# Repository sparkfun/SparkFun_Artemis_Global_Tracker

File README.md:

SparkFun Artemis Global Tracker
===============================

[*SparkFun Artemis Global Tracker (WRL-18712)*](https://www.sparkfun.com/products/18712)

The SparkFun Artemis Global Tracker combines the SparkFun Artemis processor with an Iridium 9603N satellite transceiver, ZOE-M8Q GNSS transceiver, and MS8607 PHT sensor to create a truly global tracking and data gathering device in a small form-factor. With a clear view of the sky, this board allows you to send and receive short data messages from anywhere in the world including remote locations like the polar regions, far beyond the reach of WiFi and GSM networks.

Repository Contents
-------------------

* **/Documentation** - Datasheets, FAQs, Hardware Overview, and Message Format for the full Global Tracker Example
* **/Hardware** - Eagle PCB, SCH and LBR design files
* **/Software** - Arduino examples
* **/Tools** - Tools to help: configure the full GlobalTracker example via USB or remotely via Iridium messaging; and track and map its position
* **/binaries** - binary files for the examples which you can upload using the [Artemis Firmware Upload GUI](https://github.com/sparkfun/Artemis-Firmware-Upload-GUI) instead of the Arduino IDE
* **/img** - Folder hosting for images used in the repository
* **LICENSE.md** contains the licence information

Documentation
-------------

* **[Hookup Guide](https://learn.sparkfun.com/tutorials/artemis-global-tracker-hookup-guide)** - Hookup Guide for the SparkFun Artemis Global Tracker.
* **[Artemis Development with Arduino](https://learn.sparkfun.com/tutorials/artemis-development-with-the-arduino-ide)** - An in-depth guide on developing in the Arduino IDE for the Artemis module and any Artemis microcontroller development board.
* **[SparkFun Apollo3 Arduino Core](https://github.com/sparkfun/Arduino_Apollo3)** - GitHub Repository for the SparkFun Apollo3 Arduino core.
* **[Installing an Arduino Library Guide](https://learn.sparkfun.com/tutorials/installing-an-arduino-library)** - Basic information on how to install an Arduino library.
* **[SparkFun IridiumSBD I<sup>2</sup>C Arduino Library](https://github.com/sparkfun/SparkFun_IridiumSBD_I2C_Arduino_Library)** - An Arduino library to support Short Burst Data communication using the Iridium 9602 and 9603N over both Serial and I2C.
* **[SparkFun u-blox GNSS Arduino Library](https://github.com/sparkfun/SparkFun_u-blox_GNSS_Arduino_Library)** - An Arduino library which allows you to communicate seamlessly with the full range of u-blox GNSS modules.
* **[SparkFun MS8607 Arduino Library](https://github.com/sparkfun/SparkFun_PHT_MS8607_Arduino_Library)** - An Arduino library for the TE MS8607 combined Pressure, Humidity and Temperature sensor.

Version History
---------------

* [SPX-16469](https://www.sparkfun.com/products/16469) - Initial SparkX Release
* [WRL-18712](https://www.sparkfun.com/products/18712) - Initial SparkFun Release

License Information
-------------------

This product is _**open source**_!

Please review the LICENSE.md file for license information.

If you have any questions or concerns on licensing, please contact technical support on our [SparkFun forums](https://forum.sparkfun.com/viewforum.php?f=123).

Distributed as-is; no warranty is given.

- Your friends at SparkFun.

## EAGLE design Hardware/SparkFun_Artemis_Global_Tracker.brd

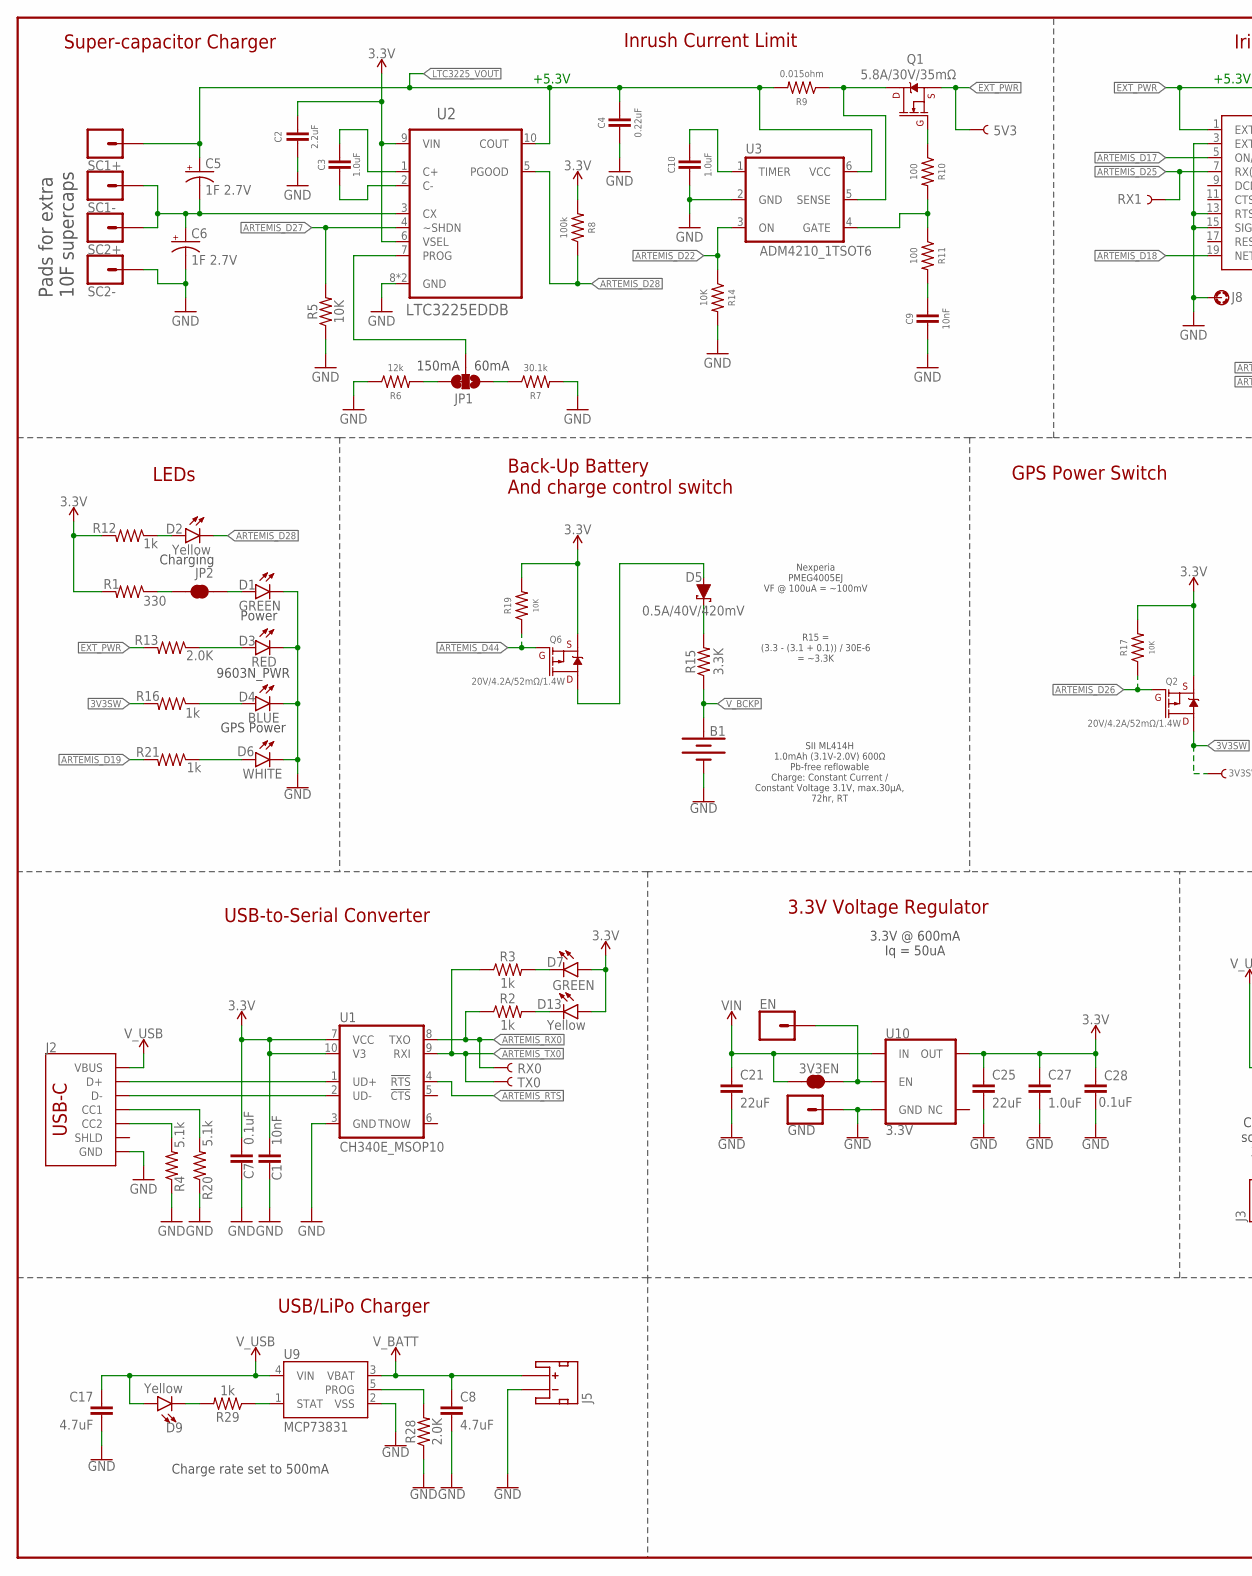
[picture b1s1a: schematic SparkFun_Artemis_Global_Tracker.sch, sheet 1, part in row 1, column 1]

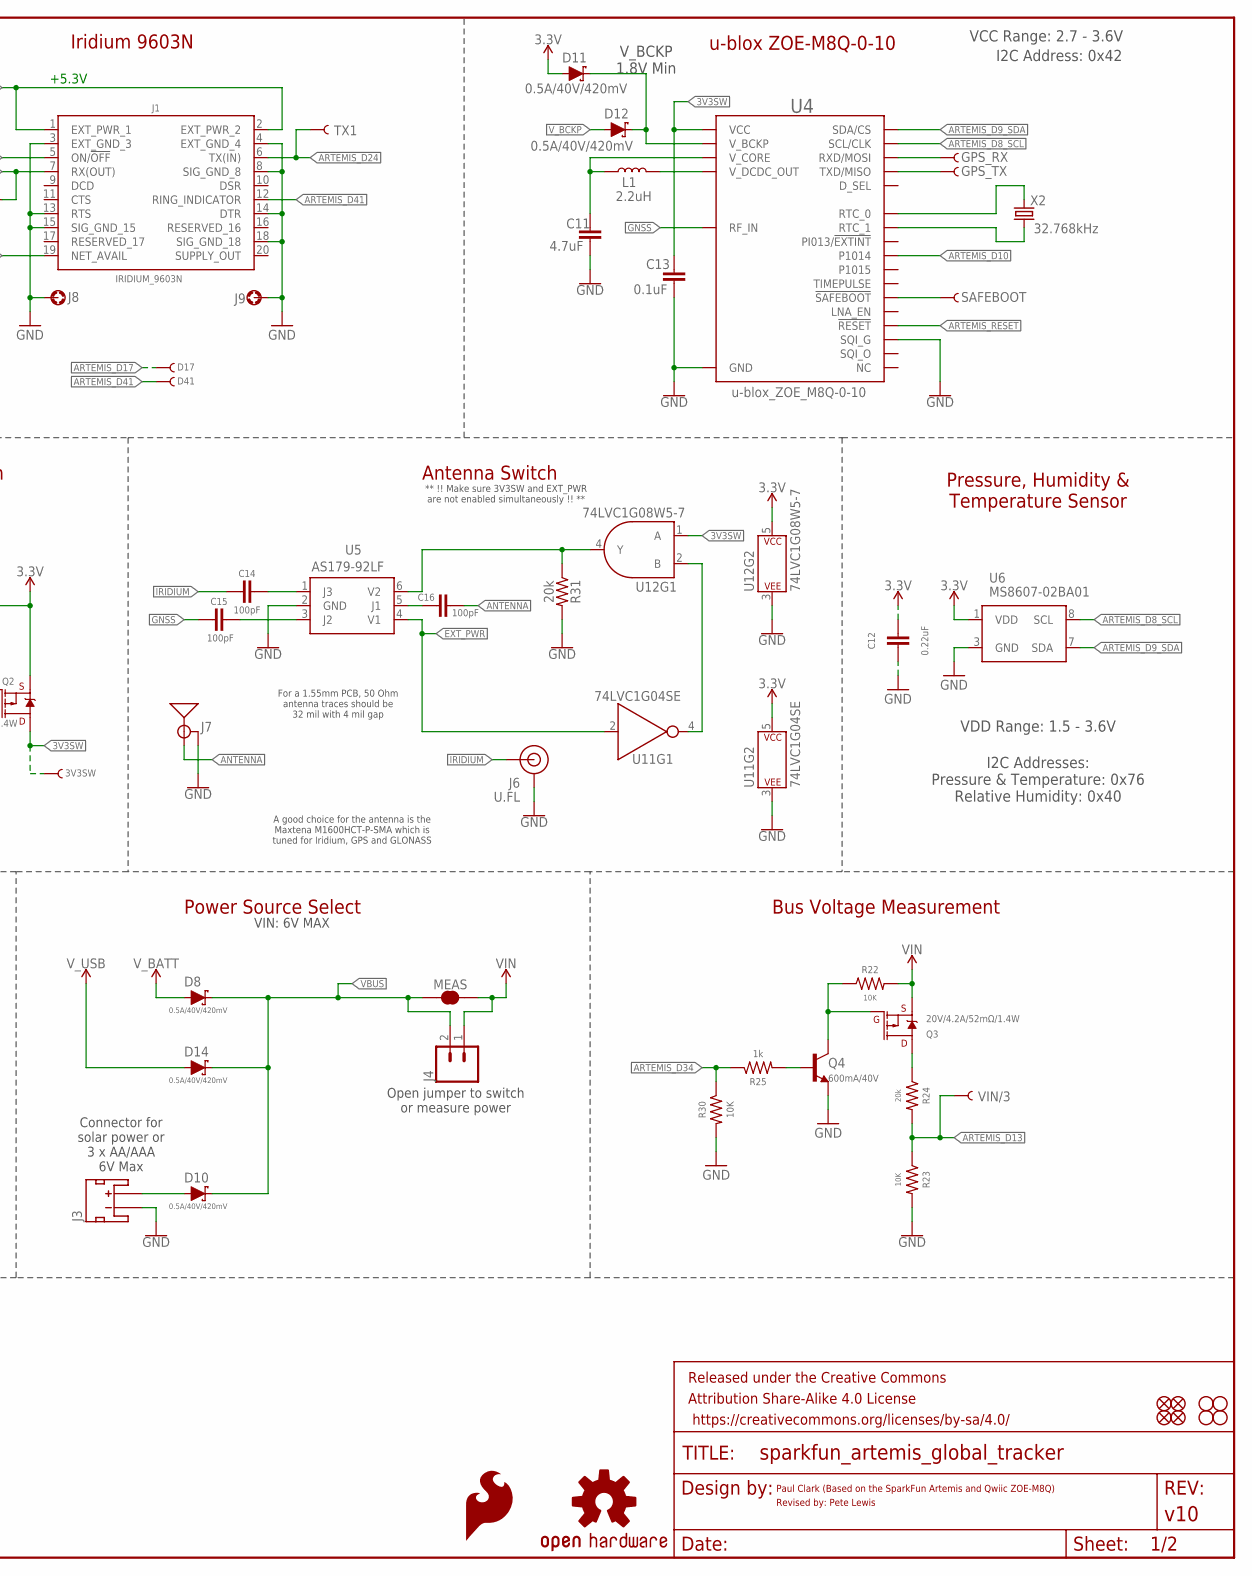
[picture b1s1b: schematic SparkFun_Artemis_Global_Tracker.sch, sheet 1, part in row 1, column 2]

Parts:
3V3EN: JUMPER-SMT_2_NC_TRACE_SILK; SMT-JUMPER_2_NC_TRACE_SILK
3V3SW, 5V3: TEST-POINT3X5; PAD.03X.05
B1: ML414H_IV01E_BATTERY; ML414H_IV01E
C1, C9: 10nF; 0603
C2: 2.2uF; 0603
C3, C10, C27: 1.0uF; 0603
C4, C12: 0.22uF; 0603
C5, C6: 1F 2.7V; CPOL-RADIAL-1F-2.7V
C7, C13, C28: 0.1uF; 0603
C8, C11, C17: 4.7uF; 0603
C14, C15, C16: 100pF; 0603
C21, C25: 22uF; 0805
D1, D7: GREEN; LED-0603
D2, D9, D13: Yellow; LED-0603
D3: RED; LED-0603
D4: BLUE; LED-0603
D5, D8, D10, D11, D12, D14: 0.5A/40V/420mV; SOD-323
D6: WHITE; LED-0603
D17, D41: TEST-POINT3X5; PAD.03X.05
EN: CONN_01PTH_NO_SILK_YES_STOP; 1X01_NO_SILK
FRAME5: FRAME-LEDGER; CREATIVE_COMMONS
GND: CONN_01PTH_NO_SILK_YES_STOP; 1X01_NO_SILK
GPS_RX: TEST-POINT3X5; PAD.03X.05
GPS_TX: TEST-POINT3X5; PAD.03X.05
J1: IRIDIUM_9603N
J2: USB-C; USB-C-16P-2LAYER-PADS
J3, J5: JST_2MM_MALE; JST-2-SMD
J4: CONN_021X02_NO_SILK; 1X02_NO_SILK
J6: U.FL
J7: ANTENNA-GROUNDEDEDGE_SMA; SMA-EDGE
J8, J9: STAND-OFF-REFLOW-M2.0_6.0MM_TALL; STAND-OFF-REFLOW-M2.0
JP1: JUMPER-SMT_3_1-NC_TRACE_SILK; SMT-JUMPER_3_1-NC_TRACE_SILK
JP2: JUMPER-SMT_2_NC_TRACE_SILK; SMT-JUMPER_2_NC_TRACE_SILK
JP7, JP8, JP13, JP14: FIDUCIAL1X2; FIDUCIAL-1X2
JP9, JP10, JP11, JP12: STAND-OFF
L1: 2.2uH; 0806
LOGO2: SFE_LOGO_FLAME.3_INCH; SFE_LOGO_FLAME_.3
LOGO4: OSHW-LOGOMINI; OSHW-LOGO-MINI
MEAS: JUMPER-SMT_2_NC_TRACE_SILK; SMT-JUMPER_2_NC_TRACE_SILK
Q1: 5.8A/30V/35mΩ; SOT23-3
Q2, Q3, Q6: 20V/4.2A/52mΩ/1.4W; SOT23-3
Q4: 600mA/40V; SOT23-3
R1: 330; 0402-TIGHT
R2, R3, R12, R16, R21, R25, R29: 1k; 0402-TIGHT
R4, R20: 5.1k; 0402-TIGHT
R5, R14, R17, R19, R22, R23, R30: 10K; 0402-TIGHT
R6: 12k; 0603
R7: 30.1k; 0603
R8: 100k; 0603
R9: 0.015ohm; 0603
R10, R11: 100; 0402-TIGHT
R13, R28: 2.0K; 0402-TIGHT
R15: 3.3K; 0402-TIGHT
R24: 20k; 0603
R31: 20k; 0402-TIGHT
RX0, RX1: TEST-POINT3X5; PAD.03X.05
SAFEBOOT: TEST-POINT3X5; PAD.03X.05
SC1+, SC1-, SC2+, SC2-: CONN_01PTH_NO_SILK_YES_STOP; 1X01_NO_SILK
TX0, TX1: TEST-POINT3X5; PAD.03X.05
U1: CH340E_MSOP10; MSOP10
U2: LTC3225EDDB; DFN300X200-10L
U3: ADM4210_1TSOT6; TSOT6
U4: u-blox_ZOE_M8Q-0-10; UBLOX_ZOE_M8-0-10
U5: AS179-92LF; SOT65P220X100-6N
U6: MS8607-02BA01
U9: MCP73831; SOT23-5
U10: 3.3V; SOT23-5
U11: 74LVC1G04SE; SOT353
U12: 74LVC1G08W5-7; SOT23-5
VIN/3: TEST-POINT3X5; PAD.03X.05
X2: 32.768kHz; CRYSTAL-SMD-3.2X1.5MM

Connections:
3.3V: C1.1, C2.1, C7.1, C12.1, C25.1, C27.1, C28.1, D7.A, D11.A, D13.A, Q2.2 (S), Q6.2 (S), R1.2, R8.2, R12.2, R17.2, R19.2, U1.7 (VCC), U1.10 (V3), U2.6 (VSEL), U2.9 (VIN), U6.1 (VDD), U10.5 (OUT), U11.5 (P$V+), U12.5 (P$V+); also elsewhere on the board
3V3SW: 3V3SW.1, C13.1, Q2.3 (D), R16.2, U4.24 (VCC), U4.25 (VCC), U12.1 (A)
ANTENNA: C16.1, J7.SIG (SIGNAL)
ARTEMIS_!RESET: U4.20 (!RESET); also elsewhere on the board
ARTEMIS_!RTS!: U1.4 (!RTS); also elsewhere on the board
ARTEMIS_D8_SCL: U4.32 (SCL/CLK), U6.8 (SCL); also elsewhere on the board
ARTEMIS_D9_SDA: U4.2 (SDA/CS), U6.7 (SDA); also elsewhere on the board
ARTEMIS_D10: U4.50 (P1014); also elsewhere on the board
ARTEMIS_D13: R23.1, R24.2, VIN/3.1; also elsewhere on the board
ARTEMIS_D17: D17.1, J1.5 (ON/!OFF!); also elsewhere on the board
ARTEMIS_D18: J1.19 (NET_AVAIL); also elsewhere on the board
ARTEMIS_D19: R21.2; also elsewhere on the board
ARTEMIS_D22: R14.1, U3.3 (ON); also elsewhere on the board
ARTEMIS_D24: J1.6 (TX(IN)), TX1.1; also elsewhere on the board
ARTEMIS_D25: J1.7 (RX(OUT)), RX1.1; also elsewhere on the board
ARTEMIS_D26: Q2.1 (G), R17.1; also elsewhere on the board
ARTEMIS_D27: R5.2, U2.4 (~SHDN); also elsewhere on the board
ARTEMIS_D28: D2.C, R8.1, U2.5 (PGOOD); also elsewhere on the board
ARTEMIS_D34: R25.1, R30.1; also elsewhere on the board
ARTEMIS_D41: D41.1, J1.12 (RING_INDICATOR); also elsewhere on the board
ARTEMIS_D44: Q6.1 (G), R19.1; also elsewhere on the board
ARTEMIS_RX0: R2.1, RX0.1, U1.8 (TXO); also elsewhere on the board
ARTEMIS_TX0: R3.1, TX0.1, U1.9 (RXI); also elsewhere on the board
CC3: J2.B5 (CC2), R4.2
CC4: J2.A5 (CC1), R20.2
D+2: J2.A6 (D+), J2.B6 (D+), U1.1 (UD+)
D-2: J2.A7 (D-), J2.B7 (D-), U1.2 (UD-)
EXT_PWR: 5V3.1, J1.1 (EXT_PWR_1), J1.2 (EXT_PWR_2), Q1.2 (S), R13.2, U5.4 (V1), U11.2 (A)
GND: B1.-, C1.2, C2.2, C4.2, C6.-, C7.2, C8.2, C9.2, C10.2, C11.2, C12.2, C13.2, C17.2, C21.2, C25.2, C27.2, C28.2, D1.C, D3.C, D4.C, D6.C, GND.1, J1.3 (EXT_GND_3), J1.4 (EXT_GND_4), J1.8 (SIG_GND_8), J1.13 (RTS), J1.14 (DTR), J1.15 (SIG_GND_15), J1.18 (SIG_GND_18), J2.GND, J2.GND2 (GND), J3.1 (-), J5.1 (-), J6.1 (GND), J6.2 (GND), J7.GND@0 (GND), J7.GND@1 (GND), J7.GND@2 (GND), J7.GND@3 (GND), J8.1, J9.1, Q4.2 (E), R4.1, R5.1, R6.1, R7.2, R14.2, R20.1, R23.2, R28.1, R30.2, R31.2, SC2-.1, U1.3 (GND), U2.8 (GND), U2.11 (GND), U3.2 (GND), U4.1 (GND), U4.3 (GND), U4.5 (GND), U4.7 (GND), U4.8 (GND), U4.9 (GND), U4.10 (GND), U4.11 (GND), U4.12 (GND), U4.17 (GND), U4.23 (GND), U4.29 (SQI_G), U4.31 (SQI_G), U4.37 (GND), U4.38 (GND), U4.39 (GND), U4.40 (GND), U4.41 (GND), U4.44 (GND), U4.46 (SQI_G), U4.47 (SQI_G), U4.49 (GND), U5.2 (GND), U6.3 (GND), U9.2 (VSS), U10.2 (GND), U11.3 (P$V-), U12.3 (P$V-); also elsewhere on the board
GNSS: C15.2, U4.4 (RF_IN)
IRIDIUM: C14.2, J6.FEED (SIGNAL)
LTC3225_VOUT: C4.1, C5.+, R9.2, SC1+.1, U2.10 (COUT), U3.6 (VCC)
unnamed: C5.-, C6.+, SC1-.1, SC2+.1, U2.3 (CX)
unnamed: JP1.3, R6.2
unnamed: JP2.2, R1.1
unnamed: JP1.1, R7.1
unnamed: D2.A, R12.1
unnamed: D3.A, R13.1
unnamed: D5.A, Q6.3 (D)
unnamed: Q1.3 (D), R9.1, U3.5 (SENSE)
unnamed: C3.2, U2.2 (C-)
unnamed: C3.1, U2.1 (C+)
unnamed: JP1.2, U2.7 (PROG)
unnamed: Q1.1 (G), R10.1
unnamed: R10.2, R11.1, U3.4 (GATE)
unnamed: C9.1, R11.2
unnamed: C10.1, U3.1 (TIMER)
unnamed: L1.2, U4.26 (V_DCDC_OUT)
unnamed: C11.1, L1.1, U4.27 (V_CORE)
unnamed: U4.18 (RTC_0), X2.P$2 (2)
unnamed: U4.19 (RTC_1), X2.P$1 (1)
unnamed: D5.C, R15.2
unnamed: D4.A, R16.1
unnamed: D13.C, R2.2
unnamed: D1.A, JP2.1
unnamed: D11.C, D12.C, U4.16 (V_BCKP)
unnamed: SAFEBOOT.1, U4.34 (!SAFEBOOT)
unnamed: GPS_RX.1, U4.22 (RXD/MOSI)
unnamed: GPS_TX.1, U4.21 (TXD/MISO)
unnamed: C14.1, U5.1 (J3)
unnamed: C15.1, U5.3 (J2)
unnamed: C16.2, U5.5 (J1)
unnamed: R31.1, U5.6 (V2), U12.4 (Y)
unnamed: D7.C, R3.2
unnamed: U11.4 (Y), U12.2 (B)
unnamed: D6.A, R21.1
unnamed: 3V3EN.2, EN.1, U10.3 (EN)
unnamed: Q3.1 (G), Q4.3 (C), R22.1
unnamed: R28.2, U9.5 (PROG)
unnamed: D9.C, R29.2
unnamed: R29.1, U9.1 (STAT)
unnamed: Q3.3 (D), R24.1
unnamed: Q4.1 (B), R25.2
VBUS: D8.C, D10.C, D14.C, J4.2, MEAS.1
VIN: 3V3EN.1, C21.1, J4.1, MEAS.2, Q3.2 (S), R22.2, U10.1 (IN)
V_AAA: D10.A, J3.2 (+)
V_BATT: C8.1, D8.A, J5.2 (+), U9.3 (VBAT)
V_BCKP: B1.+, D12.A, R15.1
V_USB: C17.1, D9.A, D14.A, J2.VBUS1 (VBUS), J2.VBUS2 (VBUS), U9.4 (VIN)

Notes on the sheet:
Paul Clark (Based on the SparkFun Artemis and Qwiic ZOE-M8Q)
Power
+5.3V
150mA
60mA
Pads for extra 10F supercaps
Super-capacitor Charger
Charging
9603N_PWR
Iridium 9603N
LEDs
Inrush Current Limit
GPS Power
u-blox ZOE-M8Q-0-10
VCC Range: 2.7 - 3.6V
I2C Address: 0x42
V_BCKP 1.8V Min
Back-Up Battery And charge control switch
SII ML414H 1.0mAh (3.1V-2.0V) 600Ω Pb-free reflowable Charge: Constant Current / Constant Voltage 3.1V, max.30μA, 72hr, RT
Nexperia PMEG4005EJ VF @ 100uA = ~100mV
R15 = (3.3 - (3.1 + 0.1)) / 30E-6 = ~3.3K
GPS Power Switch
Antenna Switch
** !! Make sure 3V3SW and EXT_PWR are not enabled simultaneously !! **
A good choice for the antenna is the Maxtena M1600HCT-P-SMA which is tuned for Iridium, GPS and GLONASS
For a 1.55mm PCB, 50 Ohm antenna traces should be 32 mil with 4 mil gap
Pressure, Humidity & Temperature Sensor
VDD Range: 1.5 - 3.6V
I2C Addresses: Pressure & Temperature: 0x76 Relative Humidity: 0x40
USB-to-Serial Converter
3.3V @ 600mA Iq = 50uA
USB/LiPo Charger
Charge rate set to 500mA
Power Source Select
Open jumper to switch or measure power
Connector for solar power or 3 x AA/AAA 6V Max
Bus Voltage Measurement
Revised by: Pete Lewis
VIN: 6V MAX
3.3V Voltage Regulator

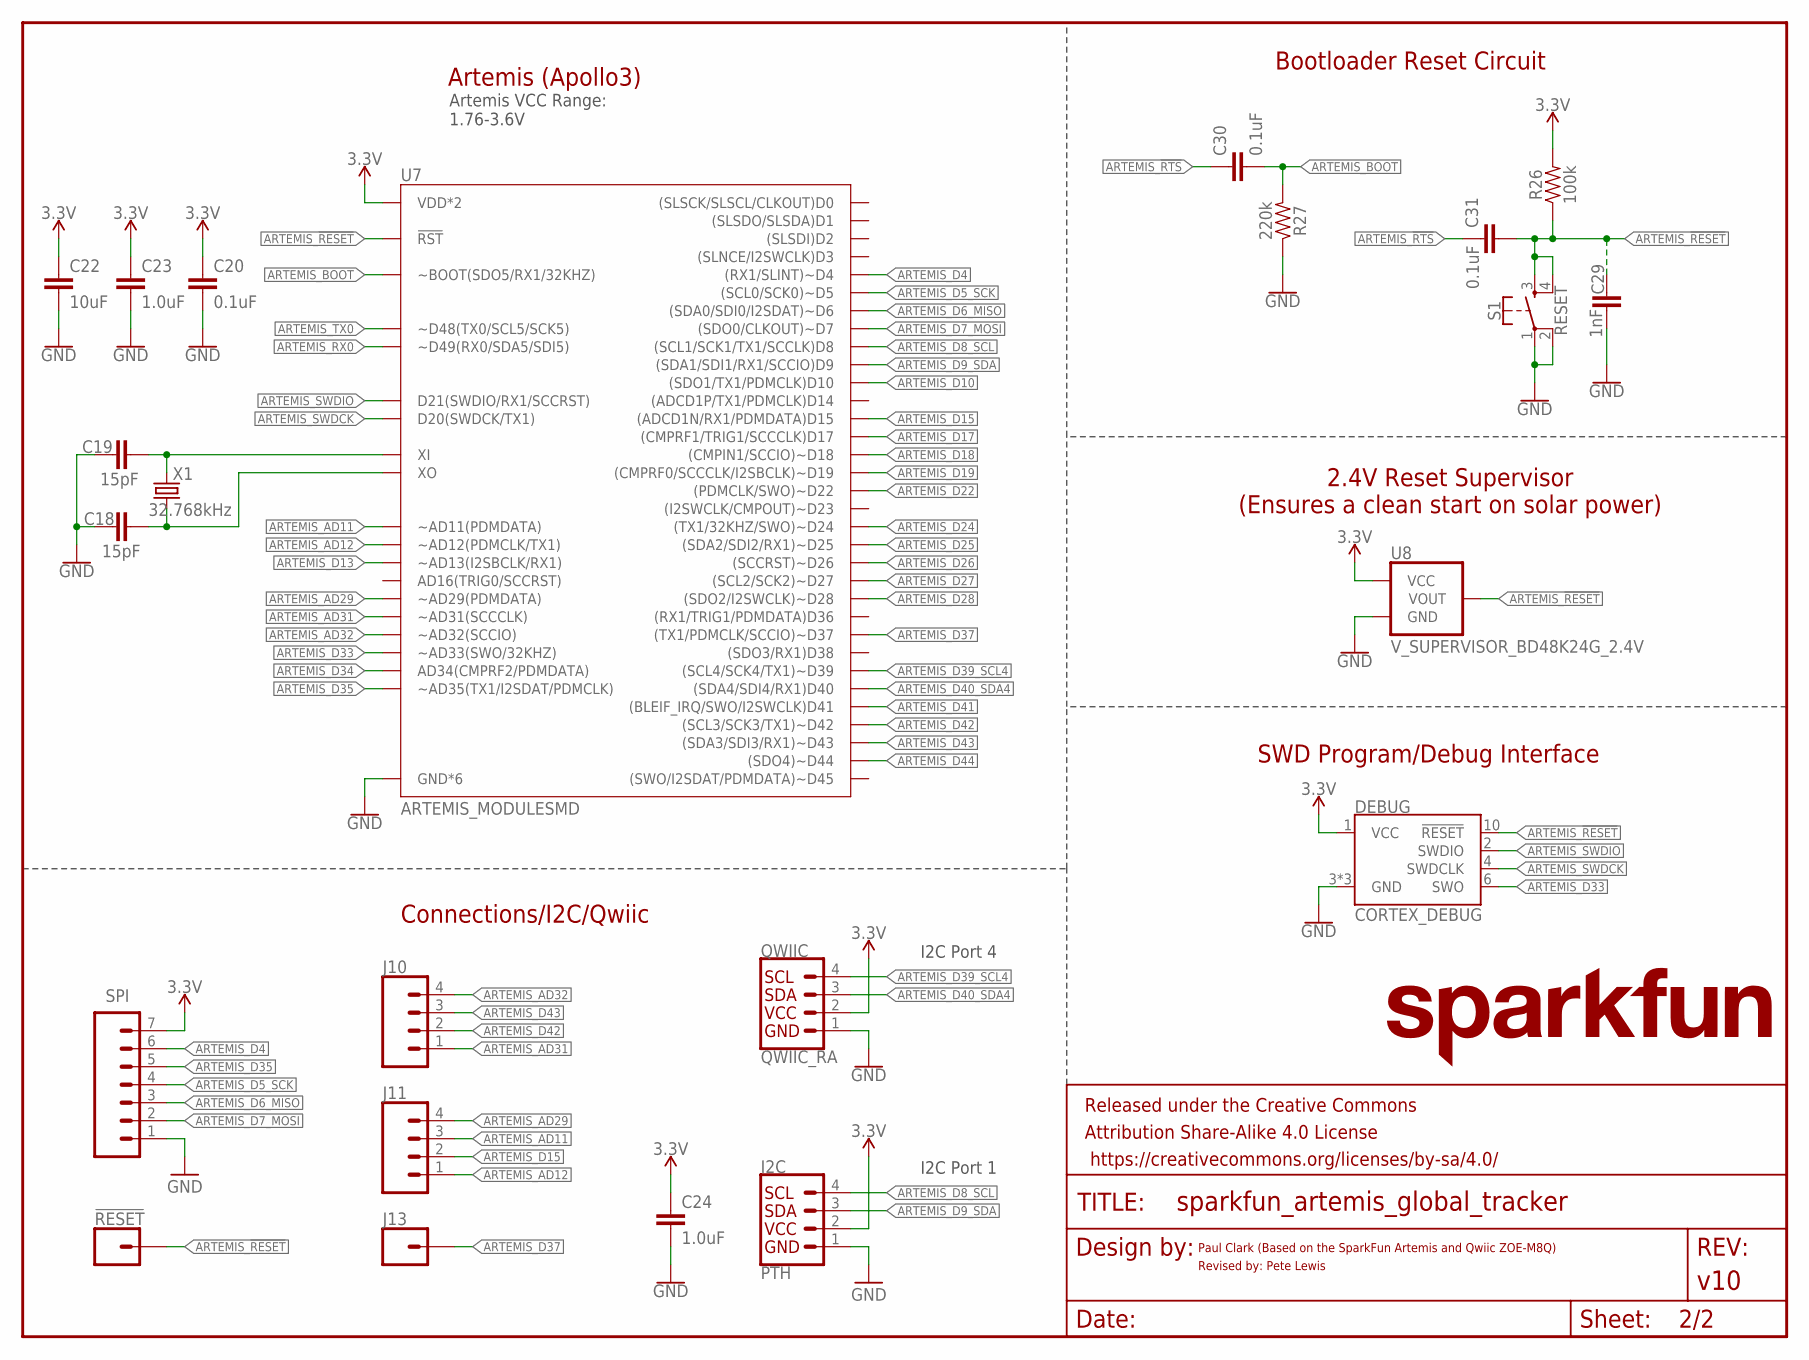
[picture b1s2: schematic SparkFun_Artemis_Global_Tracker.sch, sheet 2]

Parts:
!RESET: CONN_01PTH_NO_SILK_YES_STOP; 1X01_NO_SILK
C18, C19: 15pF; 0603
C20, C30, C31: 0.1uF; 0603
C22: 10uF; 0603
C23, C24: 1.0uF; 0603
C29: 1nF; 0603
DEBUG: CORTEX_DEBUG; 2X5-PTH-1.27MM-NO_SILK
FRAME3: FRAME-LETTERNO_PACKAGE; DUMMY
I2C: PTH; 1X04_NO_SILK
J10, J11: CONN_041X04_NO_SILK_NO_POP; 1X04_NO_SILK
J13: CONN_01PTH_NO_SILK_YES_STOP; 1X01_NO_SILK
LOGO1: SFE_LOGO_NAME.1_INCH; SFE_LOGO_NAME_.1
QWIIC: QWIIC_RA; JST04_1MM_RA
R26: 100k; 0603
R27: 220k; 0603
S1: RESET; TACTILE_SWITCH_SMD_5.2MM
SPI: CONN_07NO_SILK; 1X07_NO_SILK
U7: ARTEMIS_MODULESMD; ARTEMIS_FP
U8: V_SUPERVISOR_BD48K24G_2.4V; SOT23-3
X1: 32.768kHz; CRYSTAL-SMD-3.2X1.5MM

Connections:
3.3V: C20.2, C22.1, C23.1, C24.1, DEBUG.1 (VCC), I2C.2, QWIIC.2, R26.2, SPI.7, U7.VDD@36 (VDD*2), U7.VDD@37 (VDD*2), U8.3 (VCC); also elsewhere on the board
ARTEMIS_!RESET: !RESET.1, C29.1, C31.2, DEBUG.10 (!RESET), R26.1, S1.3, S1.4, U7.~RST (!RST), U8.2 (VOUT); also elsewhere on the board
ARTEMIS_!RTS!: C30.1, C31.1; also elsewhere on the board
ARTEMIS_AD11: J11.3, U7.~AD11 (~AD11(PDMDATA))
ARTEMIS_AD12: J11.1, U7.~AD12 (~AD12(PDMCLK/TX1))
ARTEMIS_AD29: J11.4, U7.~AD29 (~AD29(PDMDATA))
ARTEMIS_AD31: J10.1, U7.~AD31 (~AD31(SCCCLK))
ARTEMIS_AD32: J10.4, U7.~AD32 (~AD32(SCCIO))
ARTEMIS_BOOT: C30.2, R27.2, U7.BOOT (~BOOT(SDO5/RX1/32KHZ))
ARTEMIS_D4: SPI.6, U7.~D4 ((RX1/SLINT)~D4)
ARTEMIS_D5_SCK: SPI.4, U7.~D5 ((SCL0/SCK0)~D5)
ARTEMIS_D6_MISO: SPI.3, U7.~D6 ((SDA0/SDI0/I2SDAT)~D6)
ARTEMIS_D7_MOSI: SPI.2, U7.D7 ((SDO0/CLKOUT)~D7)
ARTEMIS_D8_SCL: I2C.4, U7.D8 ((SCL1/SCK1/TX1/SCCLK)D8); also elsewhere on the board
ARTEMIS_D9_SDA: I2C.3, U7.D9 ((SDA1/SDI1/RX1/SCCIO)D9); also elsewhere on the board
ARTEMIS_D10: U7.D10 ((SDO1/TX1/PDMCLK)D10); also elsewhere on the board
ARTEMIS_D13: U7.~AD13 (~AD13(I2SBCLK/RX1)); also elsewhere on the board
ARTEMIS_D15: J11.2, U7.D15 ((ADCD1N/RX1/PDMDATA)D15)
ARTEMIS_D17: U7.D17 ((CMPRF1/TRIG1/SCCCLK)D17); also elsewhere on the board
ARTEMIS_D18: U7.~D18 ((CMPIN1/SCCIO)~D18); also elsewhere on the board
ARTEMIS_D19: U7.~D19 ((CMPRF0/SCCCLK/I2SBCLK)~D19); also elsewhere on the board
ARTEMIS_D22: U7.~D22 ((PDMCLK/SWO)~D22); also elsewhere on the board
ARTEMIS_D24: U7.~D24 ((TX1/32KHZ/SWO)~D24); also elsewhere on the board
ARTEMIS_D25: U7.~D25 ((SDA2/SDI2/RX1)~D25); also elsewhere on the board
ARTEMIS_D26: U7.~D26 ((SCCRST)~D26); also elsewhere on the board
ARTEMIS_D27: U7.~D27 ((SCL2/SCK2)~D27); also elsewhere on the board
ARTEMIS_D28: U7.~D28 ((SDO2/I2SWCLK)~D28); also elsewhere on the board
ARTEMIS_D33: DEBUG.6 (SWO), U7.~AD33/SWO (~AD33(SWO/32KHZ))
ARTEMIS_D34: U7.AD34 (AD34(CMPRF2/PDMDATA)); also elsewhere on the board
ARTEMIS_D35: SPI.5, U7.~AD35 (~AD35(TX1/I2SDAT/PDMCLK))
ARTEMIS_D37: J13.1, U7.~D37 ((TX1/PDMCLK/SCCIO)~D37)
ARTEMIS_D39_SCL4: QWIIC.4, U7.~D39 ((SCL4/SCK4/TX1)~D39)
ARTEMIS_D40_SDA4: QWIIC.3, U7.D40 ((SDA4/SDI4/RX1)D40)
ARTEMIS_D41: U7.D41 ((BLEIF_IRQ/SWO/I2SWCLK)D41); also elsewhere on the board
ARTEMIS_D42: J10.2, U7.~D42 ((SCL3/SCK3/TX1)~D42)
ARTEMIS_D43: J10.3, U7.~D43 ((SDA3/SDI3/RX1)~D43)
ARTEMIS_D44: U7.~D44 ((SDO4)~D44); also elsewhere on the board
ARTEMIS_RX0: U7.RXI-0 (~D49(RX0/SDA5/SDI5)); also elsewhere on the board
ARTEMIS_SWDCK: DEBUG.4 (SWDCLK), U7.SWDCK (D20(SWDCK/TX1))
ARTEMIS_SWDIO: DEBUG.2 (SWDIO), U7.SWDIO (D21(SWDIO/RX1/SCCRST))
ARTEMIS_TX0: U7.TXO-0 (~D48(TX0/SCL5/SCK5)); also elsewhere on the board
GND: C18.1, C19.1, C20.1, C22.2, C23.2, C24.2, C29.2, DEBUG.3 (GND), DEBUG.5 (GND), DEBUG.9 (GND), I2C.1, QWIIC.1, R27.1, S1.1, S1.2, SPI.1, U7.GND@1 (GND*6), U7.GND@22 (GND*6), U7.GND@38 (GND*6), U7.GND@39 (GND*6), U7.GND@47 (GND*6), U7.GND@59 (GND*6), U8.1 (GND); also elsewhere on the board
XTALI: C19.2, U7.XI, X1.P$1 (1)
XTALO: C18.2, U7.XO, X1.P$2 (2)

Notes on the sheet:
Artemis (Apollo3)
Artemis VCC Range: 1.76-3.6V
Bootloader Reset Circuit
SWD Program/Debug Interface
Connections/I2C/Qwiic
I2C Port 1
I2C Port 4
2.4V Reset Supervisor (Ensures a clean start on solar power)
Paul Clark (Based on the SparkFun Artemis and Qwiic ZOE-M8Q)
Revised by: Pete Lewis

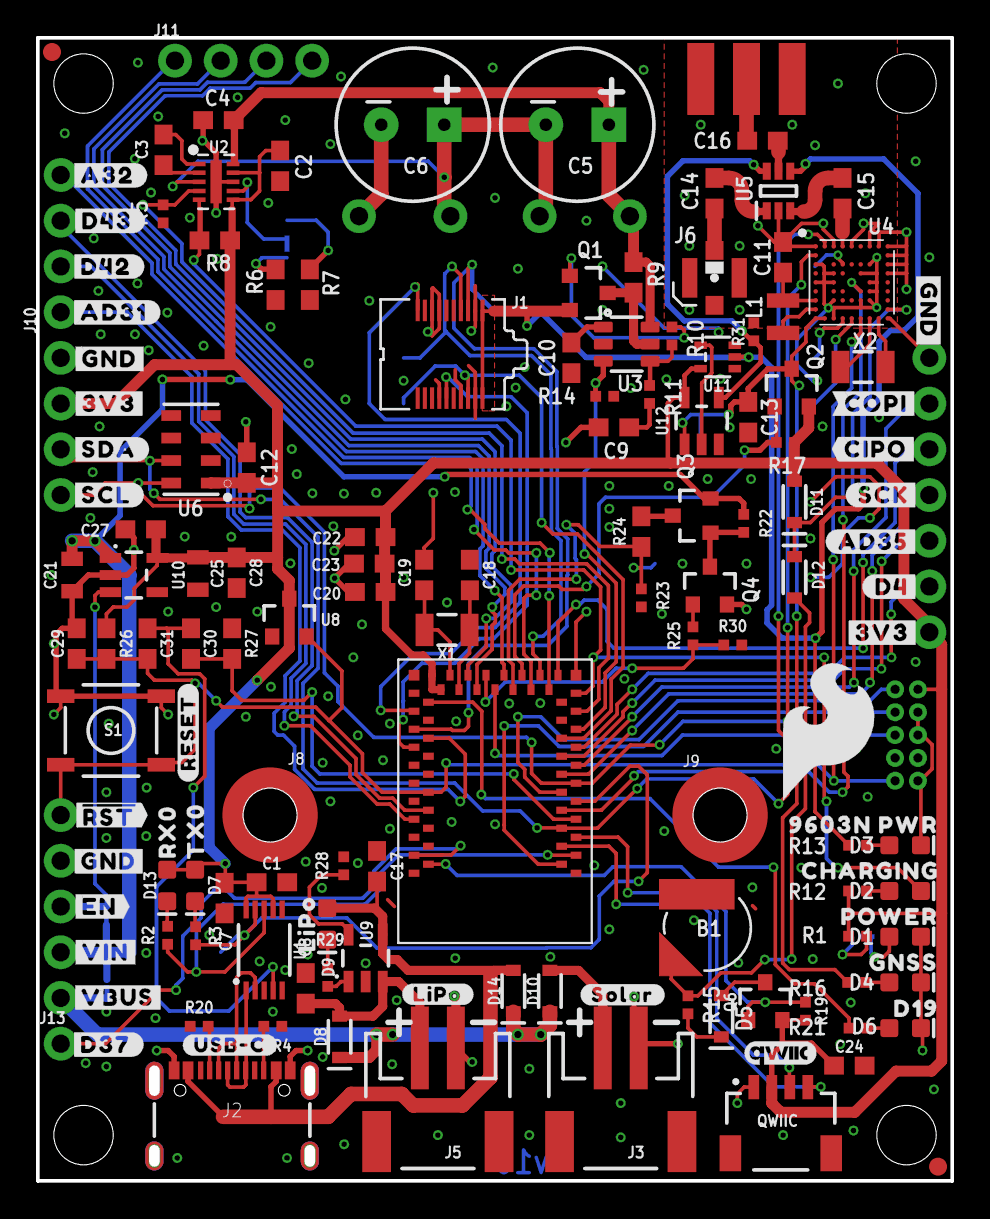
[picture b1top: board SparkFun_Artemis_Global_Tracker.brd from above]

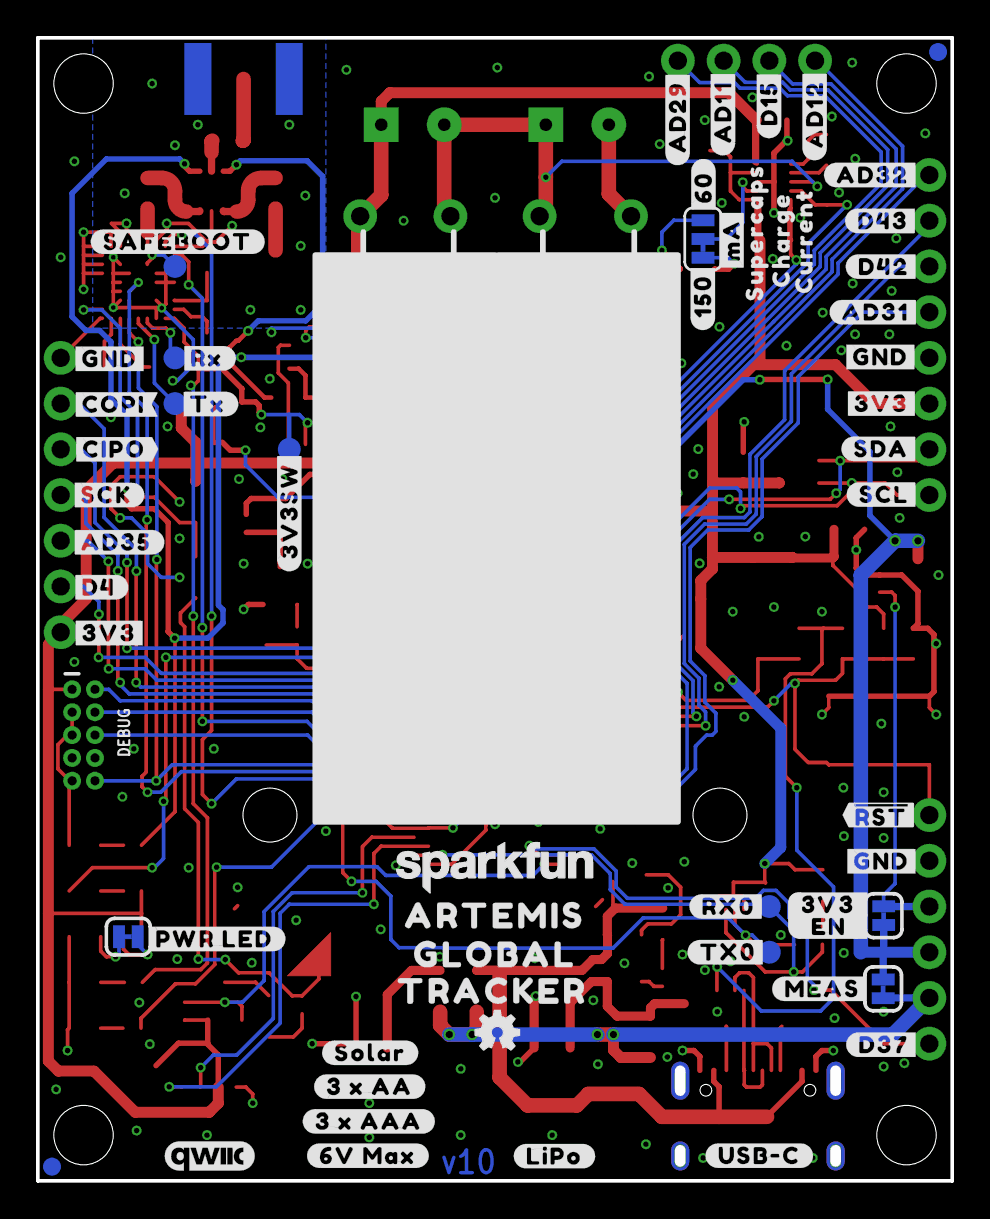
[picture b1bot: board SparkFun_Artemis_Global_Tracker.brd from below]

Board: 2 copper layers, 50.8 x 63.5 mm, 240 parts (79 on the bottom side), 101 nets.

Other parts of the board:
U$1, U$13: SUPERCAPACITOR151
U$2: #SCK#199608
U$3, U$43: #3V3#0
U$4: #SDA#0
U$5: #USB#C#0
U$6: #SCL#0
U$7: #VIN#158
U$8: #3V3SW#0
U$9: CHARGING9604
U$10: #COPI#9694
U$11: QWIIC_4MM
U$12: LIPO5
U$14, U$15: 10F_2#7V152
U$16: RX06
U$17, U$70: #3V3#153
U$18: TX07
U$19: #AD35#199609
U$20, U$36: #GND#0
U$21: #SDA#153
U$22: #SCL#154
U$24: #AD31#7
U$25: QWIIC_5MM
U$26: #_RST##156
U$27: #EN#157
U$28: #VIN#3#0
U$29: #AD35#0
U$30: ARTEMIS0
U$31: SUPERCAPS6
U$32: #D17#0
U$33: #SAFEBOOT#0
U$34: #TX0#0
U$35: #TX1#0
U$37: #RX#0
U$38: #RX1#0
U$39: #TX#0
U$40: #5#3V#0
U$41: #D41#0
U$42: #RX0#0
U$44: #RESET#162
U$45: #SOLAR#165
U$46: #LIPO#164
U$47: #MEAS#0
U$48: #3V3_#0
U$50: #D4#36
U$51: GLOBAL0
U$52: TRACKER0
U$53: #LIPO#0
U$54: #_EN_#0
U$55: #SOLAR#0
U$56: #USB#C#161
U$57: #3_X_AA#0
U$58: #VBUS#159
U$59: #AD32#152
U$60: #SCK#9696
U$61: #PWR_LED#0
U$63: #D4#5
U$64: #CIPO#2
U$65: #3_X_AAA#0
U$66: #6V_MAX#0
U$67: CHARGE8
U$69: CURRENT9
U$71: #D42#32
U$72: #D37#152
U$73: #D43#43
U$74: #150#61
U$75: #COPI#5
U$76, U$77, U$78: #GND#152
U$79: #A32#44
U$80: #MA#45
U$81: #60#46
U$82: #D43#151
U$83: #D42#151
U$84: #AD31#151
U$85: #AD12#151
U$86: #D15#151
U$87: #AD11#151
U$88: #AD29#151
U$89: #CIPO#151
U$90: #D37#0
U$91: #GND#38
U$92: ##RST##39
U$93: 9603N_PWR40
U$94: POWER9605
U$95: GNSS9606
U$96: D199607

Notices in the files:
parts and their libraries:
SparkFun-Resistors: Licensing: Creative Commons ShareAlike 4.0 International - https://creativecommons.org/licenses/by-sa/4.0
SparkFun-Aesthetics: Released under the Creative Commons Attribution Share-Alike 4.0 License
SparkFun-Aesthetics: https://creativecommons.org/licenses/by-sa/4.0
